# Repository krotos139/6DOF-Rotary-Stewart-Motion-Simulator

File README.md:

# !!! WARNING !!!

Hey. I'm making 6dof project base of https://github.com/knaufinator/6DOF-Rotary-Stewart-Motion-Simulator/tree/master/Technical

This is a DANGEROUS project, and if absolute care is not taken you will be injured or killed.

Project isn't finished yet. I will place all data to this repo.

# Experiments one

We made PCB from Christopher Knauf. And we can to control one AC motor driver:

# Projects Included
These are the components of the project that are included in this repository

## Technical 

I made all draws in Kompas 3D. I will make drawings in the future.

This is current project:

## Controller
This is an ESP32 Arduino project. This interfaces with the PC through software like simtools, after correctly configuring. This project utilizes both ESP32 cores in order to maximize refresh rates to 1000Hz, or 1ms interval. A custom MCP23S17 library is included so the outputs of all 6 motors can be set at one time instead of setting them individually, this saves time and allows for more pulses per second. This increase allows for higher movement precision on the rotational arm. There is also a filter library included, this is still in early testing.

## Simtools interface setup
Config for PC to ESP32 USB-> Serial connection within simtools, simtools will be configured to send the 6 axis parameters over to the ESP32 every 1 ms. Over a 250000 baud connection. The packet consists of 6 - 12 bit values, delimited by comma and ended by a "X" Character to signal the ESP32 that the packet is done. 

For simtools you encode the axis representations of x,y,z,Ry,Rx,RZ  with the configuration"Interface - Output" = \<Axis1a>,\<Axis2a>,\<Axis3a>,\<Axis4a>,\<Axis5a>,\<Axis6a>X   

With these settings the software package Simtools or any other custom application may communicate and command the simulator platform to move.

## Controller Schematics

We developed our controller board with optocoupler:

We use sensor bord from Christopher Knauf: 

## Controller PCB

We have a problem with USB interface. We start to do second PCB:

## TDD MMOS Schematics

We developed our TDD MMOS board with optocoupler:

## TDD MMOS PCB

We redesigned PCB for TDD MMOS. We've added optocouplers and second port extender.

## Pedal's PCB

## Platform Test Application
.Net Application for testing position limits and speed of platform. Allows for manual setting of each DOF / Axis. As well works with XBOX360 controller through the PC USB wireless adapter.

# Parts
These are some key parts I used, others can be used in their place, but variations of the AC Servo motor may not be compadible with the PCB, and may require a modified PCB schematic. 

## Electric components

* [AC Ammeter Voltmeter](https://www.aliexpress.com/item/4000589056233.html?spm=a2g0s.9042311.0.0.40e133edW2JAK5)

## Controller 
Main components on the PCB
* [ESP32 Dev board](https://aliexpress.ru/item/1005001267643044.html?spm=a2g0s.9042311.0.0.40e133edW2JAK5) - ESP32 Dev kit
* [MCP23S17-E/SP](https://www.chipdip.ru/product1/8002981432)
* [3.3V to 5V TTL Shifter Module](https://aliexpress.ru/item/32825755943.html?spm=a2g0s.9042311.0.0.40e133edW2JAK5)
* [NJK-5002C NPN NO（Normally Open)Hall Effect Sensor Switch](https://aliexpress.ru/item/32922514991.html?spm=a2g0s.9042311.0.0.40e133edW2JAK5)
* [IDC BOX HEADER 2X13 26PIN](https://aliexpress.ru/item/33009552726.html?spm=a2g0s.9042311.0.0.40e133edW2JAK5)
* [RJ45](https://aliexpress.ru/item/4000226018964.html?spm=a2g0s.9042311.0.0.40e133edW2JAK5)
* [KF301 HEADER 3 pin](https://aliexpress.ru/item/4001057723206.html?spm=a2g0s.9042311.0.0.40e133edW2JAK5)
* [KF301 HEADER 2 pin](https://aliexpress.ru/item/4001057742092.html?spm=a2g0s.9042311.0.0.40e133edW2JAK5)
* [Female Pin Header Connector](https://aliexpress.ru/item/32964870579.html?spm=a2g0s.9042311.0.0.40e133edW2JAK5)

PCB
* [Gerber files](Controller PCB Gerber/)
* [PCB Manufacturer](https://www.rezonit.ru/)

## Base
- Steel plate 8 mm thick 31” diameter
- 6 - Coupler https://amzn.to/2slOiIa

## Drive
* [6 - 750w AC servo Motors](https://www.aliexpress.com/item/32844239563.html)
* [6 - 50:1 Planetary Gears](https://www.aliexpress.com/item/32967571001.html)
*Note ensure planetary gear input diameter matches up to both the motor as well with the coupler output diameter when ordering from Aliexpress

## Connecting Arms

* [12 - Swivel head SA 12mm](https://podtrade.ru/product/42564/)
* [12 - M12 to M10 High Misalignment Angle Reducer Reducers Spacers Rod End Joint](https://www.ebay.com/itm/184116983786)
* 6 - 25x179 Steel pipe

## Swing Arms
* 6 - 25x22mm_clamp2.m3d
* 6 - 25x560 Steel pipe

## Frame 
* 16.5 meters of steel pipe

## Chassis
* [Vesa Monitor mount](https://amzn.to/2TmVS0f)
* [Coped Steel Bungs](https://amzn.to/2TGOcoo)
* [1" OD X .870 ID X .065 Wall Steel tubing](https://amzn.to/3au4FCQ)

## Extras as built in demonstration video
* [LG 34" Ultrawide](https://amzn.to/2t8YvbC)
* [Thrustmaster T16000M FCS](https://amzn.to/30qkHtY)
* [Wind Generator Fan](https://amzn.to/36W1um9)
* [Wind Generator PWM Control](https://amzn.to/2Ns1anq)
* [Wind Generator 90 Degree angle 3"-> 2" Reducer](https://amzn.to/2uN6J9z)
* [Wire Wrap](https://amzn.to/2u3jiNu)

## AC Servo motor settings for 6DoF
These are my settings on the Servo Driver aasd-15a these both enable specific modes as well define the time it should take to accelerate and decelerate the platform before it hits max speed. This is useful for when you want to protect the platform from self destruction due to the fast movements. Make them to large and the platform will feel slugish.
- pn002 - Control Mode - "002" Default
- pn003 - Servo enable - "001"
- pn033 - DSZRtriggermode - "003" Power on automatically
- pn034 - The origin return reference point model - "001" Inversion for REF(rising along the trigger)as a reference point
- pn035 - The origin back to the origin model - "000" Default
- pn036 - The origin position offset high - "011" ten thousand pulse
- pn037 - The origin position offset low - "5000" pulse
- pn038 - The origin back to the first speed - "100" R/min
- pn039 - The origin back to the second speed - "100" R/min
- pn040 - The accelerating time of origin - "050" Default
- pn041 - The origin return to slow down time - "050" Default
- pn042 - The origin in the delay - "100" ms
- pn043 - Complete the signal delay of origin - "080" Default
- pn044 - The origin return instruction execution mode - "000" Default
- pn052 - SigIn1 is "REF" - "023"
- pn053 - SigIn2 is "PSTOP" - "027"
- pn054 - SigIn3 is "PClear" - "019"
- pn055 - SigIn4 is "INH" - "020"
- pn098 - Gear - "80"
- pn109 - Position command deceleration mode- "002"
- pn110 - Position command a filtering time constant - "050"
- pn111 - S-shaped filtering time constant Ta position instruction - "50"
- pn112 - position instruction Ts S-shaped filtering

time constant Ts - "50"

Default settings:
- pn002 - Control Mode - "002"
- pn003 - Servo enable - "000"
- pn033 - DSZRtriggermode - "000"
- pn034 - The origin return reference point model - "000"
- pn035 - The origin back to the origin model - "000"
- pn036 - The origin position offset high - "000"
- pn037 - The origin position offset low - "0000"
- pn038 - The origin back to the first speed - "200" R/min
- pn039 - The origin back to the second speed - "50" R/min
- pn040 - The accelerating time of origin - "050"
- pn041 - The origin return to slow down time - "050"
- pn042 - The origin in the delay - "60" ms
- pn043 - Complete the signal delay of origin - "080"
- pn044 - The origin return instruction execution mode - "000"
- pn052 - SigIn1 is "REF" - "001"
- pn053 - SigIn2 is "PSTOP" - "002"
- pn054 - SigIn3 is "PClear" - "019"
- pn055 - SigIn4 is "INH" - "008"
- pn098 - Gear - "1"
- pn109 - Position command deceleration mode- "001"
- pn110 - Position command a filtering time constant - "050"
- pn111 - S-shaped filtering time constant Ta position instruction - "50"
- pn112 - position instruction Ts S-shaped filtering - "20"

## AC Servo motor settings for Wheel

- PN002 = 0	(control mode - voltage mode, requires restart) (Default:02)
- PN003 = 0	( Servo enabled? - external) (Default:00)
- PN018 = 0	(Take the encoder output pulse AB phase logic - 0-1) (Default:00)
- PN051 = 1500	(Motor max RPM - see motor specs) (Default:3000)
- PN053 = 18? 	(SigIn 2 port functional allocation  -27 - 27) - 58? "command reverse" function number range name
- PN188 = 159	(Analog torque instruction smooth filtering time - 1-500ms) (Default:5)
- PN189 = 39 	(Analog torque instruction gain 1-300 %/V) (Default:30)
- PN190 = 0	(Analog torque instruction offset adjustment  -1.5v - 1.5v) (Default:0)
- PN191 = 1	(Simulation of torque command direction - try 0 first) (Default:0)
- PN198 = 120 	(Torque control speed limit - 0-4500rpm) (Default:2500)

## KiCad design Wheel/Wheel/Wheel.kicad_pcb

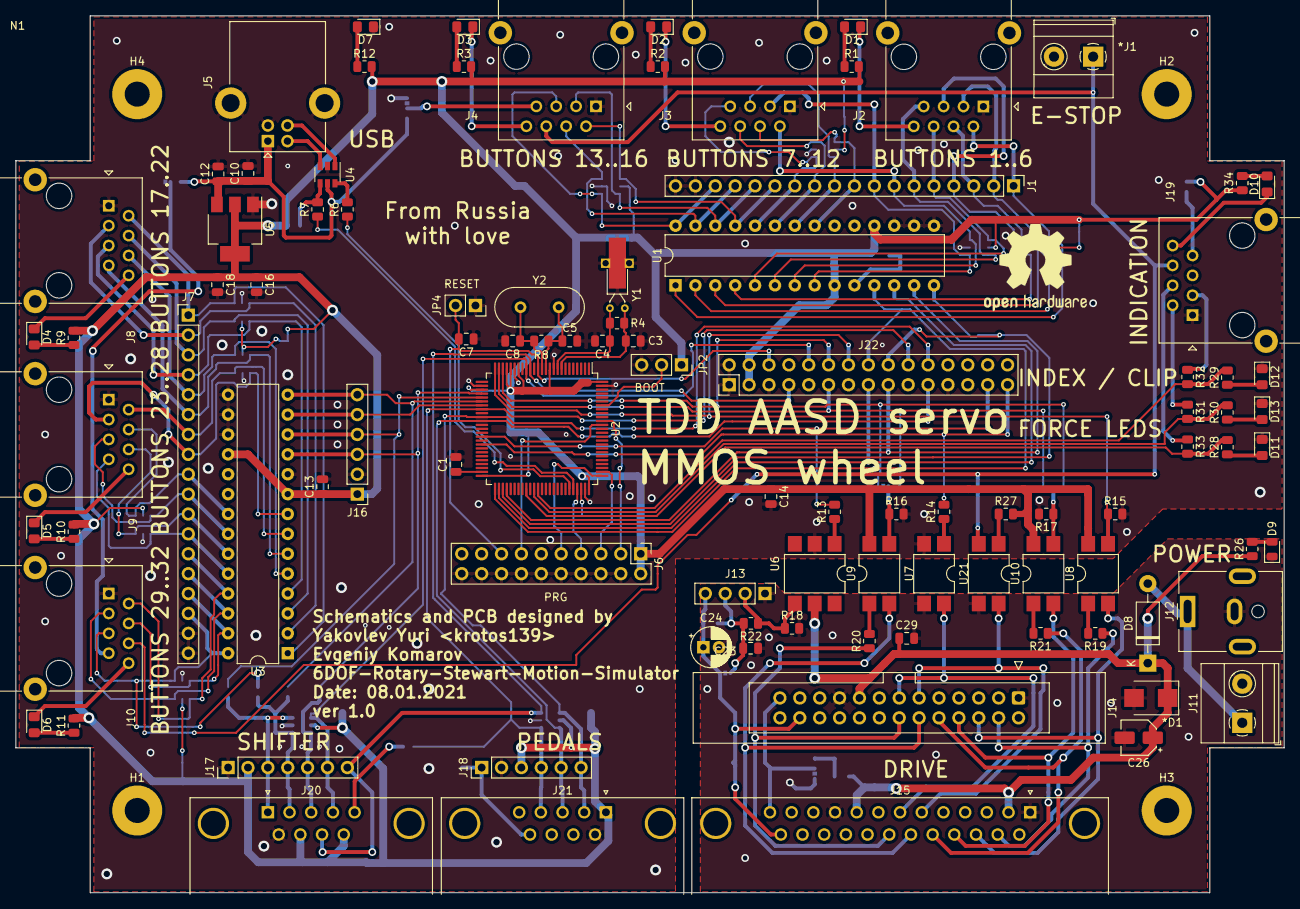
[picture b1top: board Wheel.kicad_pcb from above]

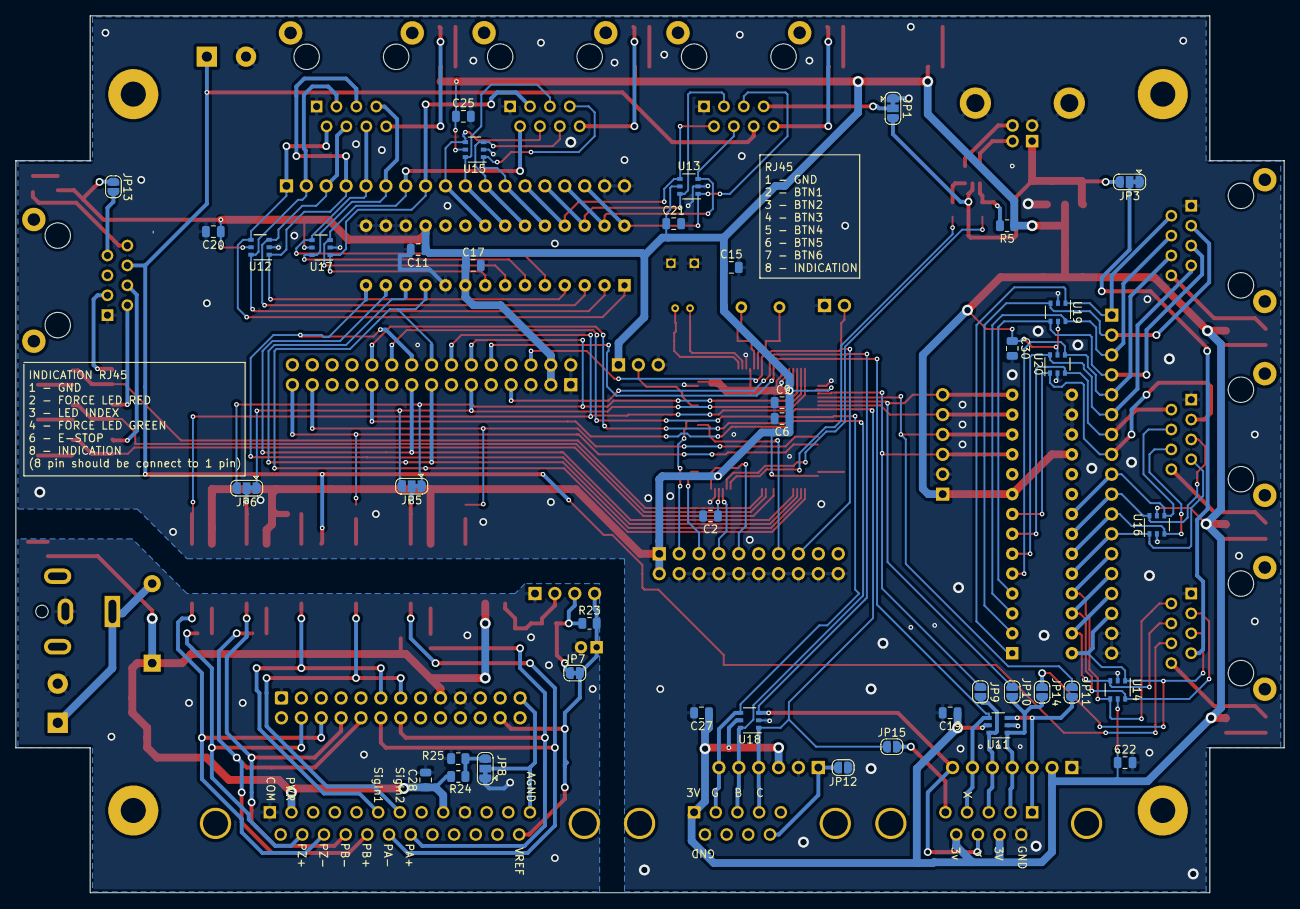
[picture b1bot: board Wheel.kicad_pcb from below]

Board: 2 copper layers, 162.0 x 112.0 mm, 145 parts (41 on the bottom side), 130 nets.

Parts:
*D1: SM6T22A; D_SMB
*J1: Screw_Terminal_01x02; TerminalBlock_Phoenix_MKDS-1,5-2_1x02_P5.00mm_Horizontal
C1, C2: 2.2uF; C_0805_2012Metric
C3, C4: 6pF; C_0805_2012Metric
C5, C8: 20pF; C_0805_2012Metric
C6, C10, C11, C13, C14, C15, C16, C17, C19, C20, C21, C22, C25, C27, C30: 104; C_0805_2012Metric
C7: 103; C_0805_2012Metric
C9, C12, C18: 10uF; C_0805_2012Metric
C23: 100nF; C_0805_2012Metric
C24: 1uF; CP_Radial_D5.0mm_P2.00mm
C26: 1uF, 50V; CP_Elec_4x5.7
C28, C29: 0.1uF 50V; C_0805_2012Metric
D1, D2, D3, D4, D5, D6, D7, D10: TO-2013BC-MRE; D_0805_2012Metric_Pad1.15x1.40mm_HandSolder
D8: 1N5818; D_DO-41_SOD81_P10.16mm_Horizontal
D9: BL-LS0805UYC; LED_0805_2012Metric
D11: TO-2013BC-PG; D_0805_2012Metric_Pad1.15x1.40mm_HandSolder
D12: TO-2013BC-BF; D_0805_2012Metric_Pad1.15x1.40mm_HandSolder
D13: TO-2013BC-MYF; D_0805_2012Metric_Pad1.15x1.40mm_HandSolder
H1, H2, H3, H4: MountingHole_Pad; MountingHole_3.2mm_M3_Pad
J1, J7: Conn_02x09_Odd_Even; PinHeader_1x18_P2.54mm_Vertical
J2, J3, J4, J8, J9, J10, J19: RJ45; RJ45_Ninigi_GE
J5: USB_B; USB_B_Lumberg_2411_02_Horizontal
J6: Conn_02x10_Odd_Even; PinHeader_2x10_P2.54mm_Vertical
J11: Screw_Terminal_01x02; TerminalBlock_Phoenix_MKDS-1,5-2_1x02_P5.00mm_Horizontal
J12: DS-201; BarrelJack_CUI_PJ-063AH_Horizontal
J13: Conn_01x04; PinHeader_1x04_P2.54mm_Vertical
J14: Conn_02x13_Top_Bottom; IDC-Header_2x13_P2.54mm_Latch_Vertical
J15: DB25_Female; DSUB-25_Female_Horizontal_P2.77x2.84mm_EdgePinOffset7.70mm_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
J16, J18: Conn_01x06; PinHeader_1x06_P2.54mm_Vertical
J17: Conn_01x07; PinHeader_1x07_P2.54mm_Vertical
J20: DB9_Male; DSUB-9_Male_Horizontal_P2.77x2.84mm_EdgePinOffset7.70mm_Hou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
J21: DB9_Female; DSUB-9_Female_Horizontal_P2.77x2.84mm_EdgePinOffset7.70mm_H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
J22: Conn_02x15_Odd_Even; PinHeader_2x15_P2.54mm_Vertical
JP1, JP3, JP5, JP6, JP8: SolderJumper_3_Bridged12; SolderJumper-3_P1.3mm_Bridged12_RoundedPad1.0x1.5mm
JP2: Jumper_3_Open; PinSocket_1x03_P2.54mm_Vertical
JP4: Jumper_2_Open; PinSocket_1x02_P2.54mm_Vertical
JP7: SolderJumper_2_Bridged; SolderJumper-2_P1.3mm_Bridged_RoundedPad1.0x1.5mm
JP9, JP10, JP11, JP12, JP13, JP14, JP15: SolderJumper_2_Open; SolderJumper-2_P1.3mm_Open_RoundedPad1.0x1.5mm
LOGO1: Logo_Open_Hardware_Large; OSHW-Logo2_14.6x12mm_SilkScreen
N1: G313; CASE_G313
R1, R2, R3, R9, R10, R11, R12, R19, R20, R21, R28, R29, R30, R31, R32, R33, R34: 330; R_0805_2012Metric
R4, R8: 10M; R_0805_2012Metric
R5: 1K5; R_0805_2012Metric
R6, R7: 22; R_0805_2012Metric
R13, R14, R27: 220; R_0805_2012Metric
R15, R16, R17, R23: 1K; R_0805_2012Metric
R18: 2K; R_0805_2012Metric
R22: 16K; R_0805_2012Metric
R24, R25: 560; R_0805_2012Metric
R26: 1k; R_0805_2012Metric
U1, U3: MCP23S17_SP; DIP-28_W7.62mm
U2: STM32F407VETx; LQFP-100_14x14mm_P0.5mm
U4: USBLC6-2SC6; SOT-23-6
U5: AMS1117; SOT-223-3_TabPin2
U6: 4N35; SMDIP-6_W7.62mm
U7, U8, U9, U10, U21: PC817; SMDIP-4_W7.62mm
U11, U12, U13, U14, U15, U16, U17, U18, U19, U20: IP4220CZ6; TSOP-6_1.65x3.05mm_P0.95mm
Y1: 32,768 кГц; Crystal_C26-LF_D2.1mm_L6.5mm_Horizontal_1EP_style2
Y2: 8MHz; Crystal_HC49-4H_Vertical

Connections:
3V: C6.1, C9.1, C11.1, C13.1, C14.1, C15.1, C16.1, C17.1, C18.1, C19.1, C20.1, C21.1, C22.1, C25.1, C27.1, C30.1, J6.1, J6.2, J16.1, J17.2, J18.3, J20.7, J20.9, J21.1, J22.3, J22.4, JP2.1, JP13.1, R1.2, R2.2, R3.2, R5.1, R9.2, R10.2, R11.2, R12.2, R27.2, R34.2, U1.9, U1.18, U2.11, U2.19, U2.21, U2.22, U2.28, U2.50, U2.75, U2.100, U3.9, U3.18, U5.2, U8.4, U9.4, U10.4, U11.5, U12.5, U13.5, U14.5, U15.5, U16.5, U17.5, U18.5, U19.5, U20.5
5V: C10.1, C12.1, J5.1, JP1.3, JP3.3, U4.5, U5.3
B1: J1.1, J2.2, U1.1, U12.4
B2: J1.2, J2.3, U1.2, U12.6
B3: J1.3, J2.4, U1.3, U12.3
B4: J1.4, J2.5, U1.4, U12.1
B5: J1.5, J2.6, U1.5, U17.4
B6: J1.6, J2.7, U1.6, U17.6
B7: J1.7, J3.2, U1.7, U17.3
B8: J1.8, J3.3, U1.8, U17.1
B9: J1.9, J3.4, U1.21, U15.4
B10: J1.10, J3.5, U1.22, U15.6
B11: J1.11, J3.6, U1.23, U15.3
B12: J1.12, J3.7, U1.24, U15.1
B13: J1.13, J4.2, U1.25, U13.4
B14: J1.14, J4.3, U1.26, U13.6
B15: J1.15, J4.4, U1.27, U13.3
B16: J1.16, J4.5, U1.28, U13.1
B17: J7.1, J8.2, U3.1, U19.1
B18: J7.2, J8.3, U3.2, U19.3
B19: J7.3, J8.4, U3.3, U19.6
B20: J7.4, J8.5, U3.4, U19.4
B21: J7.5, J8.6, U3.5, U20.4
B22: J7.6, J8.7, U3.6, U20.6
B23: J7.7, J9.2, U3.7, U20.3
B24: J7.8, J9.3, U3.8, U20.1
B25: J7.9, J9.4, U3.21, U16.4
B26: J7.10, J9.5, U3.22, U16.6
B27: J7.11, J9.6, U3.23, U16.3
B28: J7.12, J9.7, U3.24, U16.1
B29: J7.13, J10.2, U3.25, U14.4
B30: J7.14, J10.3, U3.26, U14.6
B31: J7.15, J10.4, U3.27, U14.3
B32: J7.16, J10.5, JP14.1, U3.28, U14.1
BOOT0: JP2.2, U2.94
BTN15: C3.1, R4.2, U2.8, Y1.1
BTN16: C4.1, R4.1, U2.9, Y1.2
COM: *D1.2, C23.2, C24.2, C26.2, C28.2, C29.2, D9.1, J11.2, J12.2, J13.1, J14.1, J14.19, J15.1, J15.10, JP8.1, R18.2, R25.2, U7.3, U21.3
CS: J22.16, U1.11, U2.51
DRIVE_ENABLE: *J1.1, J4.6, J10.6, J19.6, U21.2
DRIVE_PA+: J14.14, J15.20, R20.1
DRIVE_PA-: J14.12, J15.19, U9.2
DRIVE_PB+: J14.10, J15.18, R21.1
DRIVE_PB-: J14.8, J15.17, U10.2
DRIVE_PZ+: J14.4, J15.15, R19.1
DRIVE_PZ-: J14.6, J15.16, U8.2
DRIVE_SigIn1: J14.11, J15.6, U21.4
DRIVE_SigIn2: J14.13, J15.7, U7.4
DRIVE_VREF: C24.1, J13.4, J14.24, J15.25, JP7.2, R23.2
DRV_DIR: J22.29, R14.2, U2.42
DRV_PWM: J22.27, R13.2, U2.40
ENC_A: J22.12, JP5.1, JP6.3, U2.23
ENC_B: J22.11, JP5.3, JP6.1, U2.24
ENC_I: J22.14, R15.1, U2.25, U8.3
FORCE_LED_B: R29.2, R32.2, U2.62
FORCE_LED_G: R28.2, R33.2, U2.59
FORCE_LED_R: R30.2, R31.2, U2.61
GND: *J1.2, C1.2, C2.2, C3.2, C4.2, C5.2, C6.2, C7.1, C8.2, C9.2, C10.2, C11.2, C12.2, C13.2, C14.2, C15.2, C16.2, C17.2, C18.2, C19.2, C20.2, C21.2, C22.2, C25.2, C27.2, C30.2, D7.1, D11.1, D12.1, D13.1, J1.17, J1.18, J2.1, J3.1, J4.1, J5.4, J5.5, J6.4, J6.6, J6.8, J6.10, J6.12, J6.14, J6.16, J6.18, J6.20, J7.17, J7.18, J8.1, J9.1, J10.1, J16.2, J17.1, J18.2, J19.1, J20.6, J21.6, J22.1, J22.2, J22.5, J22.23, JP1.1, JP2.3, JP3.1, JP4.1, JP12.1, R15.2, R16.2, R17.2, U1.10, U1.15, U1.16, U1.17, U2.10, U2.20, U2.27, U2.74, U2.99, U3.10, U3.15, U3.16, U3.17, U4.2, U5.1, U6.2, U7.2, U11.2, U12.2, U13.2, U14.2, U15.2, U16.2, U17.2, U18.2, U19.2, U20.2, Y1.3
unnamed: C1.1, U2.49
unnamed: C2.1, U2.73
unnamed: C23.1, J13.3, JP7.1, R22.2, R23.1
unnamed: D1.1, J2.8
unnamed: D1.2, R1.1
unnamed: D2.1, J3.8
unnamed: D2.2, R2.1
unnamed: D3.1, J4.8
unnamed: D3.2, R3.1
unnamed: D4.1, J8.8
unnamed: D4.2, R9.1
unnamed: D5.1, J9.8
unnamed: D5.2, R10.1
unnamed: D6.1, J10.8
unnamed: D6.2, R11.1
unnamed: D7.2, R12.1
unnamed: D9.2, R26.2
unnamed: D10.1, J19.8
unnamed: D10.2, R34.1
unnamed: D11.2, R28.1
unnamed: D12.2, R29.1
unnamed: D13.2, R30.1
unnamed: J4.7, JP1.2
unnamed: J5.2, U4.3
unnamed: J5.3, U4.1
unnamed: J10.7, JP3.2
unnamed: J13.2, R18.1, R22.1, U6.4
unnamed: J14.25, J15.13, JP8.2
unnamed: J18.1, J21.9, JP12.2
unnamed: J19.2, R31.1
unnamed: J19.3, R32.1
unnamed: J19.4, R33.1
unnamed: J19.7, JP13.2
unnamed: J20.5, JP15.2
unnamed: JP5.2, R16.1, U9.3
unnamed: JP6.2, R17.1, U10.3
unnamed: JP8.3, R24.2, R25.1
unnamed: R5.2, R7.2, U4.4
unnamed: R6.2, U4.6
unnamed: R13.1, U6.1
unnamed: R14.1, U7.1
unnamed: R19.2, U8.1
unnamed: R20.2, U9.1
unnamed: R21.2, U10.1
unnamed: R27.1, U21.1
OSC_IN: C5.1, R8.2, U2.12, Y2.1
OSC_OUT: C8.1, R8.1, U2.13, Y2.2
PA13: J6.7, U2.72
PA14: J6.9, U2.76
PA15: J6.5, U2.77
PB3: J6.13, U2.89
PB4: J6.3, U2.90
PEDAL_BREAK: J18.5, J21.3, J22.21, U2.36, U18.6
PEDAL_CLUCH: J18.4, J21.4, J22.20, JP15.1, U2.33, U18.1
PEDAL_GAS: J18.6, J21.2, J22.22, U2.35, U18.4
PWR: *D1.1, C26.1, C28.1, C29.1, D8.1, J14.17, J15.2, J15.9, R24.1, R26.1, U6.5
PWR_IN: D8.2, J11.1, J12.1
RESET: C7.2, J6.15, J22.6, JP4.2, U2.14
SCK: J22.15, U1.12, U2.52
SHIFTER_X: J17.6, J20.4, J22.10, U2.17, U11.4
SHIFTER_Y: J17.7, J20.8, J22.7, U2.16, U18.3
SI: J22.17, U1.13, U2.54
SO: J22.18, U1.14, U2.53
SPI1_CS: J16.3, JP9.1, U2.29, U3.11
SPI1_CS_PROT: J17.5, J20.3, JP9.2, U11.6
SPI1_SCK: J16.4, JP11.1, U2.30, U3.12
SPI1_SCK_PROT: J17.3, J20.1, JP11.2, U11.3
SPI1_SI: J16.5, U2.32, U3.13
SPI1_SO: J16.6, JP10.1, U2.31, U3.14
SPI1_SO_PROT: J17.4, J20.2, JP10.2, JP14.2, U11.1
USB_DM: R6.1, U2.70
USB_DP: R7.1, U2.71

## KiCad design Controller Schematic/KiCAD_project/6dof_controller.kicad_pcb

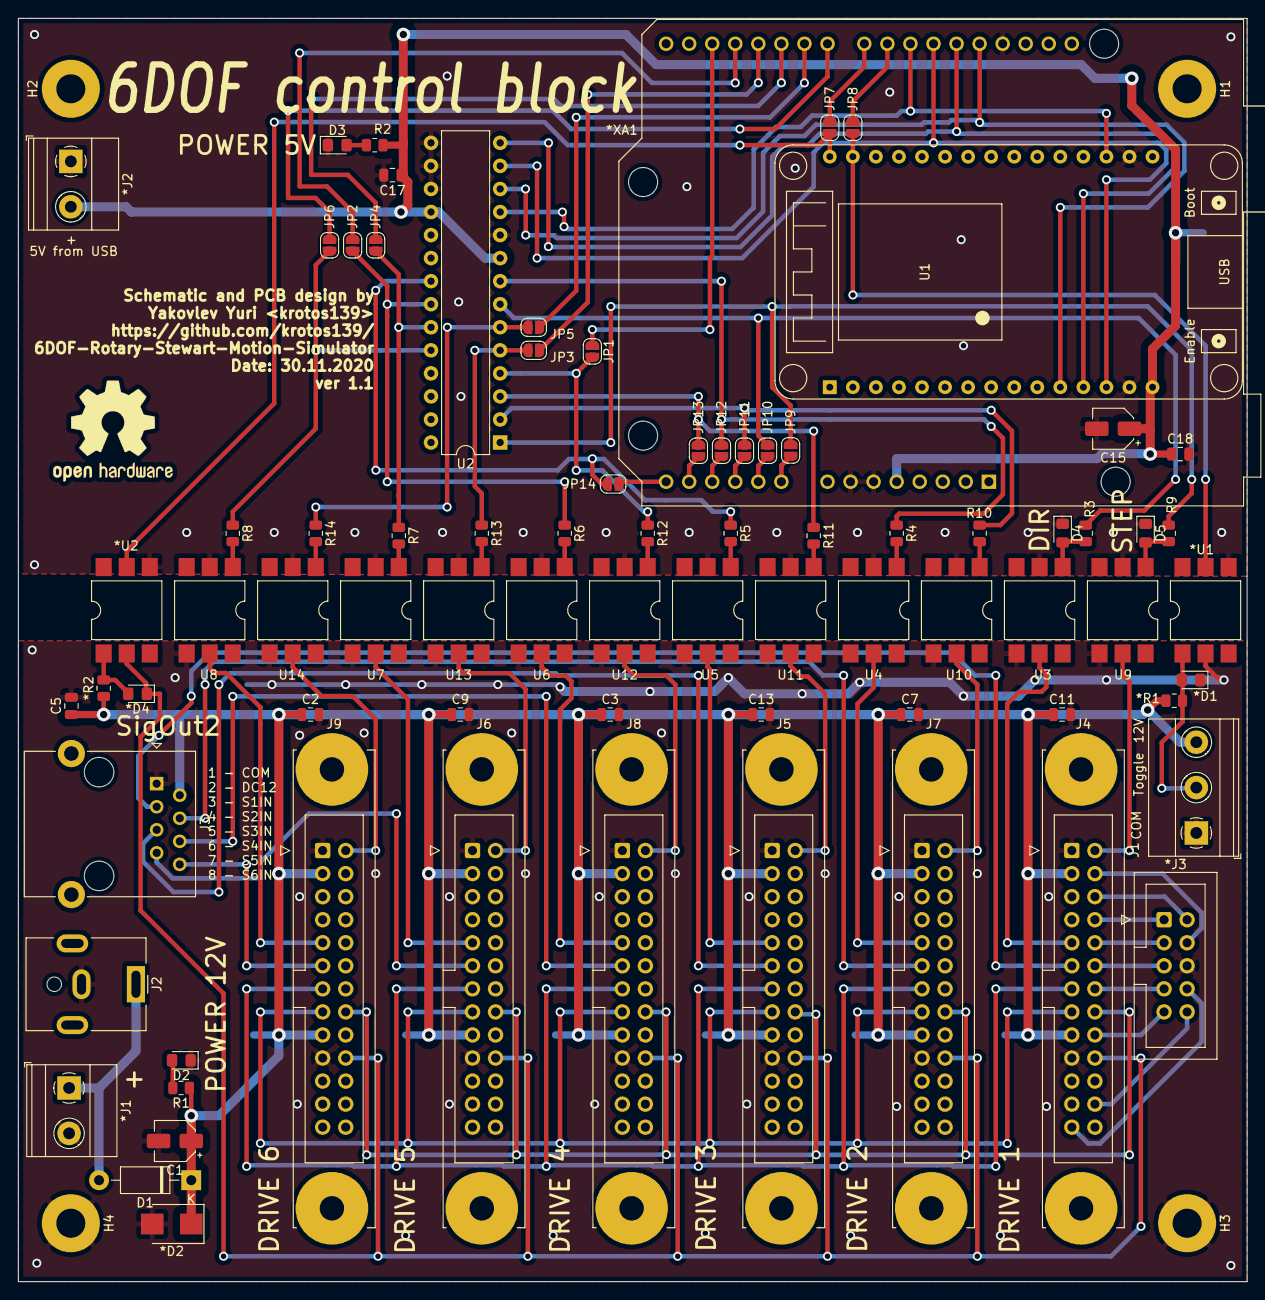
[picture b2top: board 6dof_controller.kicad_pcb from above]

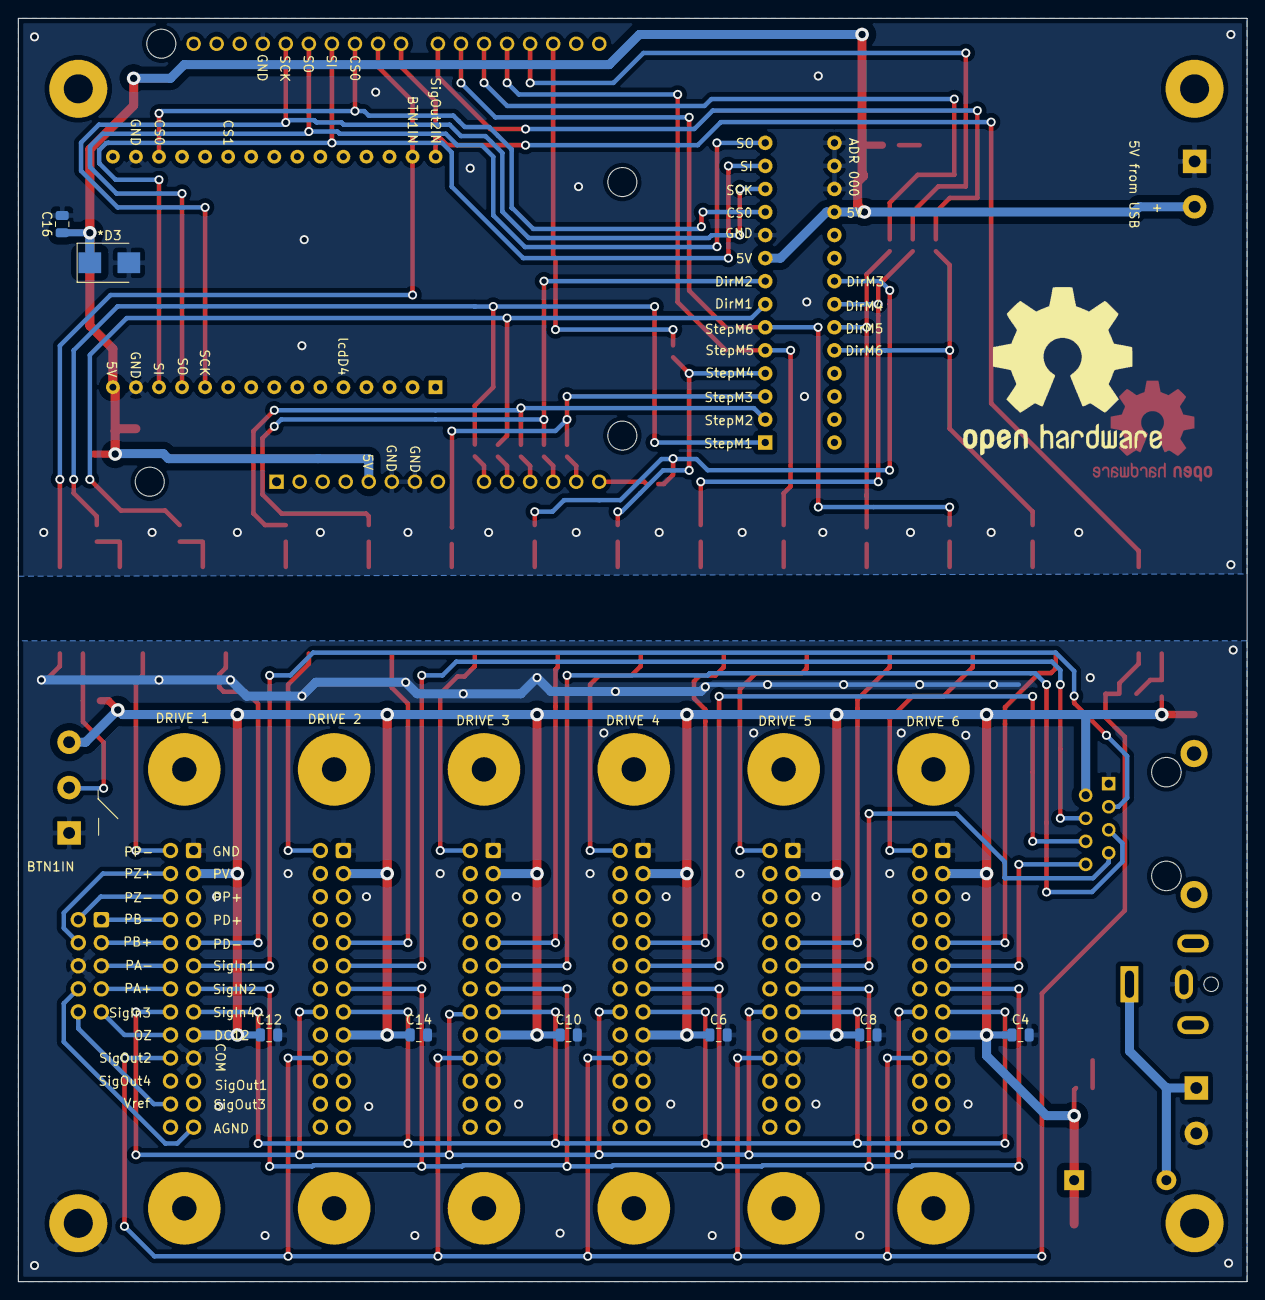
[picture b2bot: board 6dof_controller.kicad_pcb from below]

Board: 2 copper layers, 135.4 x 139.2 mm, 91 parts (8 on the bottom side), 84 nets.

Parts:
*D1, *D4: BL-LS0805UYC; LED_0805_2012Metric_Pad1.15x1.40mm_HandSolder
*D2, *D3: SM6T22A; D_SMB
*J1, *J2: Screw_Terminal_01x02; TerminalBlock_Phoenix_MKDS-1,5-2_1x02_P5.00mm_Horizontal
*J3: Conn_02x05_Top_Bottom; IDC-Header_2x05_P2.54mm_Vertical
*R1, *R2: 330; R_0805_2012Metric
*U1, *U2: 4N35; SMDIP-6_W9.53mm
*XA1: Arduino_Uno_Shield; Arduino_UNO_R3_WithMountingHoles
C1, C15: 1uF, 50V; CP_Elec_4x5.7
C2, C3, C4, C5, C6, C7, C8, C9, C10, C11, C12, C13, C14, C16, C17, C18: 0.1uF 50V; C_0805_2012Metric
D1: 1N4003; D_DO-41_SOD81_P10.16mm_Horizontal
D2, D3, D4, D5: BL-LS0805UYC; LED_0805_2012Metric_Pad1.15x1.40mm_HandSolder
H1, H2, H3, H4: MountingHole_Pad; MountingHole_3.2mm_M3_Pad
J1: Screw_Terminal_01x03; TerminalBlock_Phoenix_MKDS-1,5-3_1x03_P5.00mm_Horizontal
J2: DS-201; BarrelJack_CUI_PJ-063AH_Horizontal
J3: RJ45; RJ45_Ninigi_GE
J4, J5, J6, J7, J8, J9: Conn_02x13_Top_Bottom; IDC-Header_2x13-1MP_P2.54mm_Latch_Vertical
JP1, JP2, JP3, JP4, JP5, JP6, JP7, JP8, JP9, JP10, JP11, JP12, JP13, JP14: SolderJumper_2_Open; SolderJumper-2_P1.3mm_Open_RoundedPad1.0x1.5mm
LOGO1: Logo_Open_Hardware_Large; OSHW-Logo2_14.6x12mm_Copper
R1: 1K; R_0805_2012Metric
R2: 330; R_0805_2012Metric
R3, R4, R5, R6, R7, R8, R9, R10, R11, R12, R13, R14: 100; R_0805_2012Metric
U1: ESP32_DevKit_V1_DOIT; esp32_devkit_v1_doit
U2: MCP23SigIn1M17_SP; DIP-28_W7.62mm
U3, U4, U5, U6, U7, U8, U9, U10, U11, U12, U13, U14: 4N35; SMDIP-6_W9.53mm

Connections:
5V: *D3.1, *J2.2, *XA1.5, C15.1, C16.1, C17.1, C18.1, R2.1, U1.15, U2.9, U2.18
/DirM1: JP10.2, R3.1, U2.7
/DirM2: JP12.2, R4.1, U2.8
/DirM3: JP14.2, R5.1, U2.21
/DirM4: JP2.2, R6.1, U2.22
/DirM5: JP4.2, R7.1, U2.23
/DirM6: JP6.2, R8.1, U2.24
/StepM1: JP9.2, R9.1, U2.1
/StepM2: JP11.2, R10.1, U2.2
/StepM3: JP13.2, R11.1, U2.3
/StepM4: JP1.2, R12.1, U2.4
/StepM5: JP3.2, R13.1, U2.5
/StepM6: JP5.2, R14.1, U2.6
BTN1IN: *U1.5, JP8.2, U1.29
COM: *D1.1, *D2.2, *J1.2, *J3.6, *U1.2, C1.2, C2.2, C3.2, C4.2, C5.2, C6.2, C7.2, C8.2, C9.2, C10.2, C11.2, C12.2, C13.2, C14.2, D2.1, H3.1, H4.1, J1.1, J2.2, J3.1, J4.1, J4.19, J5.1, J5.19, J6.1, J6.19, J7.1, J7.19, J8.1, J8.19, J9.1, J9.19, U3.4, U4.4, U5.4, U6.4, U7.4, U8.4, U9.4, U10.4, U11.4, U12.4, U13.4, U14.4
CS0: *XA1.25, U1.18, U2.11
DC12: *D2.1, *R1.2, *R2.1, C1.1, C2.1, C3.1, C4.1, C5.1, C6.1, C7.1, C8.1, C9.1, C10.1, C11.1, C12.1, C13.1, C14.1, D1.1, J1.3, J3.2, J4.3, J4.17, J5.3, J5.17, J6.3, J6.17, J7.3, J7.17, J8.3, J8.17, J9.3, J9.17, R1.1
DM1: J4.9, U3.5
DM2: J7.9, U4.5
DM3: J5.9, U5.5
DM4: J8.9, U6.5
DM5: J6.9, U7.5
DM6: J9.9, U8.5
Earth_Protective: *D3.2, *J2.1, *U1.4, *U2.4, *XA1.6, *XA1.7, *XA1.29, C15.2, C16.2, C17.2, C18.2, D3.1, D4.1, D5.1, U1.14, U1.17, U2.10, U2.15, U2.16, U2.17, U3.2, U4.2, U5.2, U6.2, U7.2, U8.2, U9.2, U10.2, U11.2, U12.2, U13.2, U14.2
unnamed: *D1.2, *R1.1, *U1.1, J1.2
unnamed: *D4.2, *R2.2, *U2.1
unnamed: *J1.1, D1.2, J2.1
unnamed: *J3.1, J4.8
unnamed: *J3.2, J4.6
unnamed: *J3.3, J4.10
unnamed: *J3.4, J4.4
unnamed: *J3.5, J4.12
unnamed: *J3.7, J4.14
unnamed: *J3.8, J4.25
unnamed: *J3.9, J4.18
unnamed: *J3.10, J4.24
unnamed: *XA1.9, JP9.1
unnamed: *XA1.10, JP10.1
unnamed: *XA1.11, JP11.1
unnamed: *XA1.12, JP12.1
unnamed: *XA1.13, JP13.1
unnamed: *XA1.14, JP14.1
unnamed: *XA1.17, JP1.1
unnamed: *XA1.18, JP2.1
unnamed: *XA1.19, JP3.1
unnamed: *XA1.20, JP4.1
unnamed: *XA1.21, JP5.1
unnamed: *XA1.22, JP6.1
unnamed: *XA1.23, JP7.1
unnamed: *XA1.24, JP8.1
unnamed: D2.2, R1.2
unnamed: D3.2, R2.2
unnamed: D4.2, R3.2, U3.1
unnamed: D5.2, R9.2, U9.1
unnamed: R4.2, U4.1
unnamed: R5.2, U5.1
unnamed: R6.2, U6.1
unnamed: R7.2, U7.1
unnamed: R8.2, U8.1
unnamed: R10.2, U10.1
unnamed: R11.2, U11.1
unnamed: R12.2, U12.1
unnamed: R13.2, U13.1
unnamed: R14.2, U14.1
SCK: *XA1.28, U1.11, U2.12
SI: *XA1.26, U1.13, U2.13
SM1: J4.2, U9.5
SM2: J7.2, U10.5
SM3: J5.2, U11.5
SM4: J8.2, U12.5
SM5: J6.2, U13.5
SM6: J9.2, U14.5
SO: *XA1.27, U1.12, U2.14
SigIn1M1: J3.3, J4.11
SigIn1M2: J3.4, J7.11
SigIn1M3: J3.5, J5.11
SigIn1M4: J3.6, J8.11
SigIn1M5: J3.7, J6.11
SigIn1M6: J3.8, J9.11
SigIn2: J4.13, J5.13, J6.13, J7.13, J8.13, J9.13
SigIn3: J4.16, J5.16, J6.16, J7.16, J8.16, J9.16
SigIn4: J4.15, J5.15, J6.15, J7.15, J8.15, J9.15
SigOut2: *D4.1, *U2.2, J4.20, J5.20, J6.20, J7.20, J8.20, J9.20
SigOut2IN: *U2.5, JP7.2, U1.30

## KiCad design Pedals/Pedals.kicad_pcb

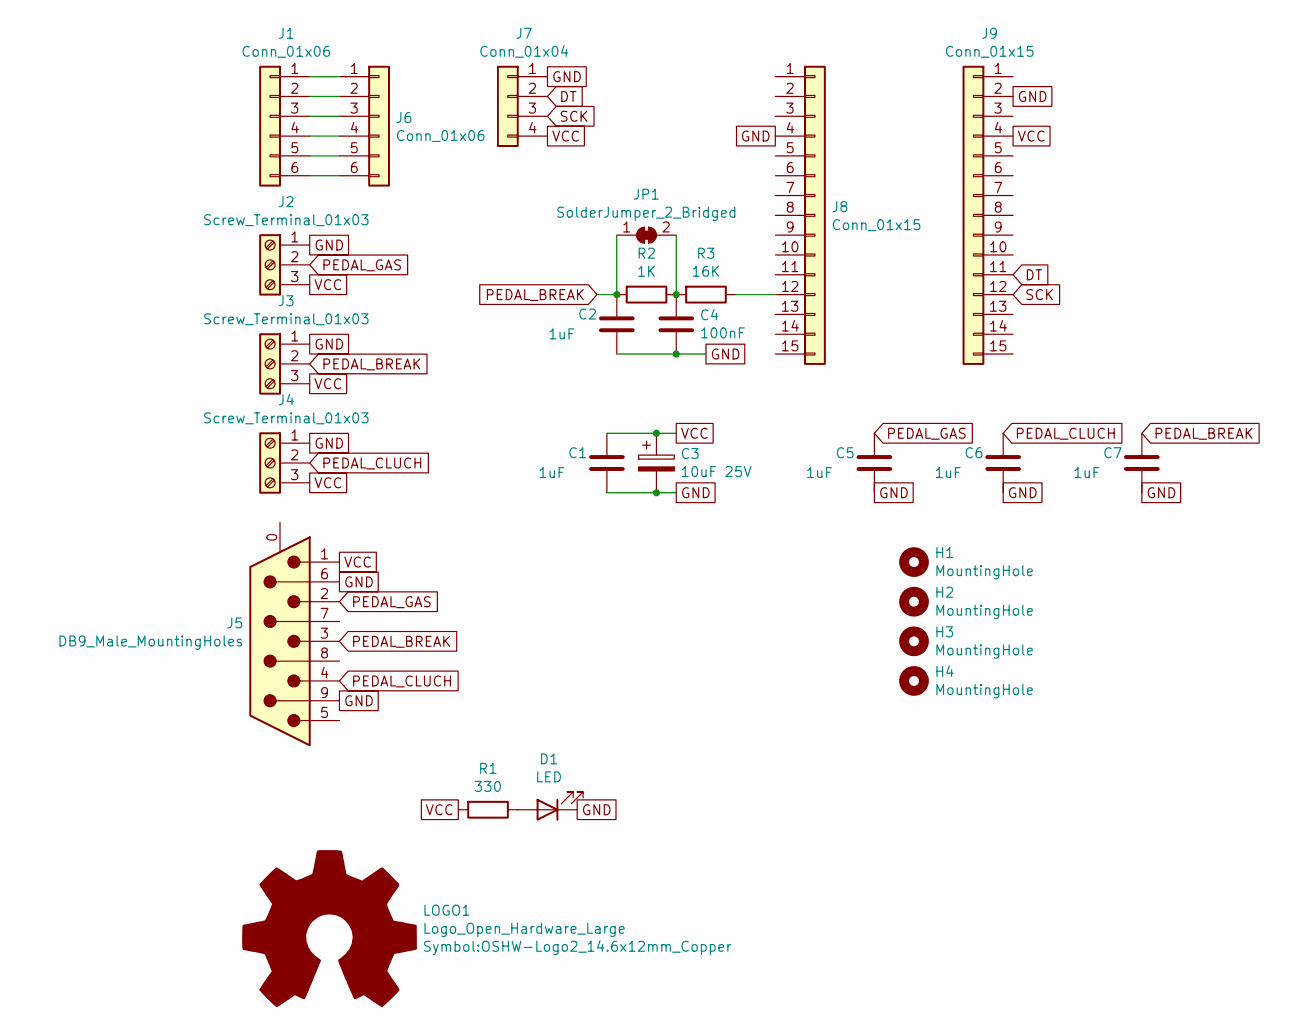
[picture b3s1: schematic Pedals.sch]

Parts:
C1, C2, C5, C6, C7: 1uF; C_0805_2012Metric
C3: 10uF 25V; CP_Elec_5x5.4
C4: 100nF; C_0805_2012Metric
D1: LED; LED_0805_2012Metric
H1, H2, H3, H4: MountingHole; MountingHole_2.5mm_Pad
J1: Conn_01x06; PinHeader_1x06_P2.54mm_Vertical
J2, J3, J4: Screw_Terminal_01x03; TerminalBlock_Phoenix_MKDS-1,5-3_1x03_P5.00mm_Horizontal
J5: DB9_Male_MountingHoles; DSUB-9_Male_Horizontal_P2.77x2.84mm_EdgePinOffset4.94mm_Hou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
J6: Conn_01x06; PinSocket_1x06_P2.54mm_Vertical
J7: Conn_01x04; PinSocket_1x04_P2.54mm_Vertical
J8, J9: Conn_01x15; PinSocket_1x15_P2.54mm_Vertical
JP1: SolderJumper_2_Bridged; SolderJumper-2_P1.3mm_Bridged_RoundedPad1.0x1.5mm
LOGO1: Logo_Open_Hardware_Large; OSHW-Logo2_14.6x12mm_Copper
R1: 330; R_0805_2012Metric
R2: 1K; R_0805_2012Metric
R3: 16K; R_0805_2012Metric

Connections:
DT: J7.2, J9.11
GND: C1.2, C2.2, C3.2, C4.2, C5.2, C6.2, C7.2, D1.1 (K), J2.1, J3.1, J4.1, J5.6, J5.9, J7.1, J8.4, J9.2
unnamed: C4.1, JP1.2 (B), R2.1, R3.2
unnamed: D1.2 (A), R1.1
unnamed: J1.1, J6.1
unnamed: J1.2, J6.2
unnamed: J1.3, J6.3
unnamed: J1.4, J6.4
unnamed: J1.5, J6.5
unnamed: J1.6, J6.6
unnamed: J8.12, R3.1
PEDAL_BREAK: C2.1, C7.1, J3.2, J5.3, JP1.1 (A), R2.2
PEDAL_CLUCH: C6.1, J4.2, J5.4
PEDAL_GAS: C5.1, J2.2, J5.2
SCK: J7.3, J9.12
VCC: C1.1, C3.1, J2.3, J3.3, J4.3, J5.1, J7.4, J9.4, R1.2

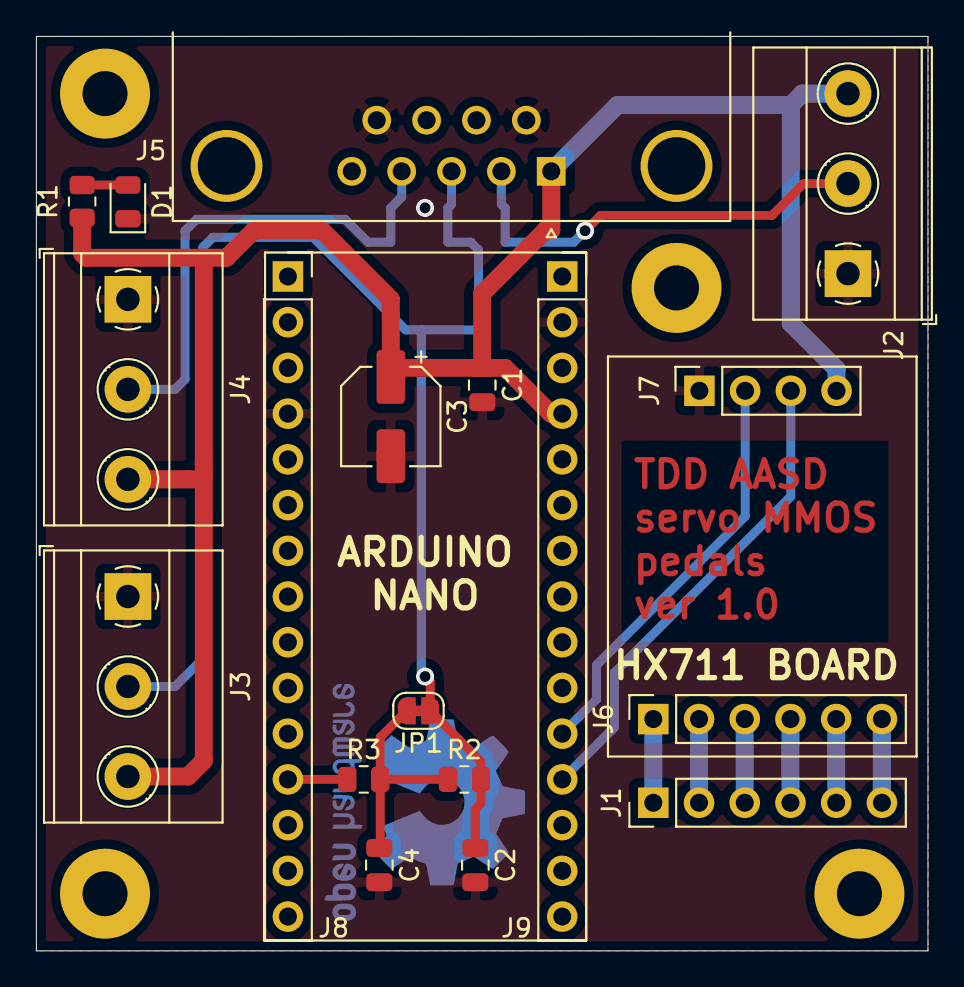
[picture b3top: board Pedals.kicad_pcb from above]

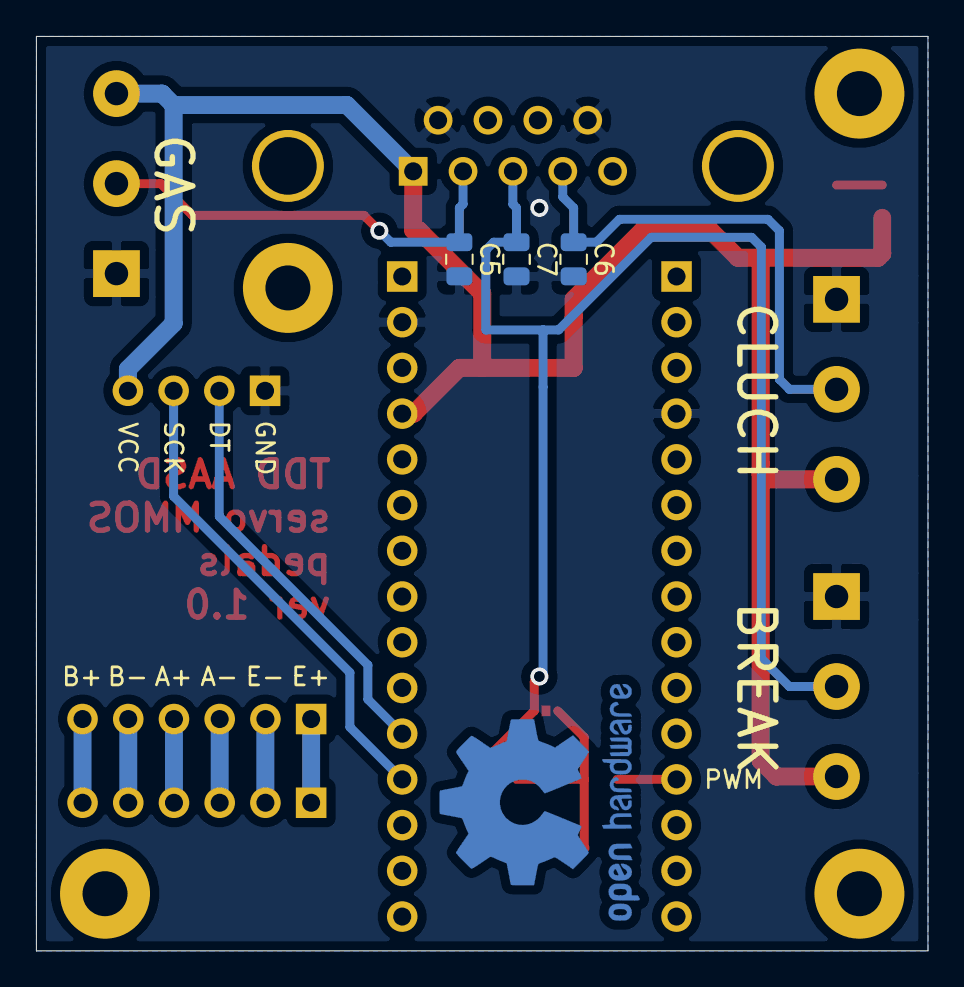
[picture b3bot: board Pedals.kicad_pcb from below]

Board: 2 copper layers, 49.5 x 50.8 mm, 26 parts (4 on the bottom side), 16 nets.

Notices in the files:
Controller Schematic/111/111.kicad_pcb:
Licence: GPL v3
